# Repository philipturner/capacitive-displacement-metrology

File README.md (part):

# Capacitive Displacement Metrology

Phase 0.2/I/II of the [APM Roadmap](https://github.com/philipturner/apm-roadmap)

Objective: Finish a project that has dragged on for 14 months.

Deadline: April 31, 2026 for creepless imaging of graphite

Table of Contents:
- [December 15, 2025](#december-15-2025)
- [December 16, 2025](#december-16-2025)
- [December 18, 2025](#december-18-2025)
- [December 22, 2025](#december-22-2025)
- [January 3, 2026](#january-3-2026)
- [January 5, 2026](#january-5-2026)
- [January 6, 2026](#january-6-2026)
- [January 7, 2026](#january-7-2026)
- [January 8, 2026](#january-8-2026)
- [January 9, 2026](#january-9-2026)
- [January 12, 2026](#january-12-2026)
- [January 13, 2026](#january-13-2026)
- [January 14, 2026](#january-14-2026)
- [January 15, 2026](#january-15-2026)
- [January 16, 2026](#january-16-2026)
- [January 20, 2026](#january-20-2026)
- [January 24, 2026](#january-24-2026)
- [January 26, 2026](#january-26-2026)
- [January 29, 2026](#january-29-2026)
- [January 30, 2026](#january-30-2026)
- [February 2, 2026](#february-2-2026)
- [February 3, 2026](#february-3-2026)
- [February 11, 2026](#february-11-2026)
- [February 12, 2026](#february-12-2026)
- [February 17, 2026](#february-17-2026)
- [February 27, 2026](#february-27-2026)
- [March 8, 2026](#march-8-2026)
- [March 9, 2026](#march-9-2026)
- [March 10, 2026](#march-10-2026)
- [March 12, 2026](#march-12-2026)
- [March 20, 2026](#march-20-2026)
- [March 26, 2026](#march-26-2026)
- [March 28, 2026](#march-28-2026)
- [March 29, 2026](#march-29-2026)
- [April 2, 2026](#april-2-2026)
- [April 27, 2026](#april-27-2026)
- [May 4, 2026](#may-4-2026)
- [Jun 1, 2026](#jun-1-2026)
- [Jun 7, 2026](#jun-7-2026)
- [Jun 17, 2026](#jun-17-2026)

## December 15, 2025

$80,000 worth of wire transfers have hit the bank. I now have enough financial security to proceed with hardware work.

The first step is ensuring I can be paid a full-time salary. Comply with US tax laws, SEC regulations, etc. I predicted the exact numbers before going through the legal boilerplate and setup.

To save effort, serious work <i>probably</i> won't begin until Jan 2 2026. I can avoid filing a few tax return documents for the 2025 year. I will figure out some remaining tax and paperwork stuff during the last days of 2025.

Current estimate for the press release is Dec 18 2025.

## December 16, 2025

This is ridiculous. The United States is the only country where taxes are such a pain: https://www.propublica.org/article/inside-turbotax-20-year-fight-to-stop-americans-from-filing-their-taxes-for-free

## December 18, 2025

I want to make the creepless SPM happen in the shortest amount of time, and publish transparent data that can be fact-checked. To stay true to my motive, I made another attempt to persuade Robert Wolkow to cooperate. I could save many person-hours, recycling existing designs for creepless SPM hardware.

Regardless of whether he shares any design information, I will proceed according to plan. Any data published by other sources should be treated with extreme skepticism. Do not trust any other lab's data, except data gathered in my own house.

| Phase | Description | Voltage |
| ----: | ----------- | ------: |
| 0.2   | PZT metrology | 24&ndash;40 V |
| 1.1   | LiNbO3 metrology | 850 V |
| 1.2   | LiNbO3 kinematic mount | 850 V |
| 2.1   | LiNbO3 STM, graphite sample | 850 V |
| 2.2   | LiNbO3 STM, inverted mode tip registration | 850 V |

I can shortcut to an important milestone, without the expensive vacuum chamber. Just need to speed up the progress with tripod synthesis. No additional employees or contractors needed for hardware design.

At the end of Phase 0.2, we'll reflect on how long this phase took. If it happened quickly, we can reach the end goal with a single employee. Otherwise, I will probably hire a temporary contractor for hardware design. Phase 2.2 should be completed before Dec 31 2026.

> Nomenclature change: exclude Roman numerals from the phase names, at least when numbering sub-phases. It's highly cumbersome to process "I.1" and "II.2", versus "1.1" and "2.2".
>
> In addition, we may right-align the phase names in tables and spreadsheets.

## December 22, 2025

Still figuring out taxes, but making progress. Putting work on the next MNT animation on hold. Not really motivated when the response to the tutorial is anemic.

Figuring out the details of a possible contract with ChimiaDAO. Our funds should last us well beyond 6 months into the future: oversee completion of Phase 0.2, stable income while raising funds for the next round. Progress on the tripod synthesis will be reported in the Phase 0.2 repository, alongside hardware progress.

## January 3, 2026

We are now sufficiently ready to return to experiments. Paid labor will start on January 5. Rippling costs a ridiculous $1,800 sign-on contract over 18 months ($150 down payment). Definitely not what they publicly advertise or what you get from LLM summaries. In the future, we will face similar obfuscation of quotes from hardware suppliers (e.g. UHV-quality turbopumps cost $14,000 minimum).

## January 5, 2026

I will start by resolving an important unknown. How much does it cost to have 500 nm range instead of 80 nm range for the LiNbO3 piezos? This has implications all through Phase III, where we integrate a custom scanner into the vacuum chamber. It explodes the design cost in Phase III because Wolkow will likely be selling his own design. Already designed hardware is cheaper than the person-hours cost of designing new hardware.

https://www.matsusada.com/corporate/management.html

Might contact Matsusada after doing my own research on their products and my performance requirements.

https://www.matsusada.com/column/hvps-safty.html

### Modeling Power Supply Requirements

To be conservative, assume we'll need 3 kinematic mounts for X, Y, and Z. We're also reducing the range, with 6 plates from Wolkow's patent instead of 10. Now all actuators, for all axes, use 6-high piezo stacks. The capacitance of the kinematic mount probably prevents utilization of the PA94 for high slew rates.

Design options for piezo stack geometry:
- 6 plates, 5 mm x 5 mm area, 6 mm stack height
- 6 plates, 10 mm x 10 mm area, 6 mm stack height
- 10 plates, 10 mm x 10 mm area, 10 mm stack height

The plate area is important now, because smaller plates have less capacitance, and thus lower current pulse requirements for the power supply. We may also use different plate areas for the fine vs. coarse actuators. Mechanically, sticking two 5 mm x 5 mm stacks on top of each other would create a 12 mm high tower. Not a good idea.

### Modeling Piezo Force Requirements

To break static friction, the piezo needs to generate a certain amount of force. In addition to the range and waveform frequency requirements.

Assuming a 0.5 mm thick plate and 69.2 GPa shear modulus:

| Voltage | Displacement | Shear Proportion | Shear Pressure |
| ------: | -----------: | ---------------: | -------------: |
| 200 V   | 13.6 nm      | 2.72e-5          | 1.88e6 Pa      |
| 850 V   | 57.8 nm      | 1.16e-4          | 8.00e6 Pa      |

Forces for various setups at 200 V:

| Plate Size | Plate Count | Shear Force | Max Weight |
| ---------- | ----------: | ----------: | ---------: |
| 5 mm x 5 mm   | 1 | 47.1 N | 4.8 kg |
| 5 mm x 5 mm   | 3 | 141.1 N | 14.4 kg |
| 10 mm x 10 mm | 1 | 188.2 N | 19.2 kg |
| 10 mm x 10 mm | 3 | 564.7 N | 57.6 kg |

Forces for various setups at 850 V:

| Plate Size | Plate Count | Shear Force |
| ---------- | ----------: | ----------: |
| 5 mm x 5 mm   | 1 | 200.0 N | 20.4 kg |
| 5 mm x 5 mm   | 3 | 600.0 N | 61.2 kg |
| 10 mm x 10 mm | 1 | 800.0 N | 81.6 kg |
| 10 mm x 10 mm | 3 | 2399.9 N | 244.9 kg |

Even though shear force doesn't increase with the number of plates per stack, the above numbers should exceed all reasonable force requirements.

### Modeling Required Slew Rate

Dive deeper into the waveform requirements for stick-slip nanopositioning:
- Does the waveform need to contain components above the resonance frequency?
- What is the target rate in steps/second?
- Why is woodpecker coarse tip approach so slow?

These variables can probably be resolved at a later date. I mostly want a lower capacitance in the kinematic mount, while still attaining 30 V/μs slew rate of the PA95 op amp.

### Design Space Exploration

Quiescent current demands on power supply:
- Conservatively 6 DAC channels and 6 PA95 op amps for Phase III
- 6 * 2.2 mA = 13.2 mA

Capacitance (in pF) of entire kinematic mount:
- Piezo plate count is 18 (3 stacks, each with 6 plates)
- Dielectric constant of lithium niobate at 300 K is 88
- Thickness of each plate is 0.5 mm

| Configuration | Capacitance |
| ------------- | ----------: |
| 5 mm x 5 mm   | 701         |
| 10 mm x 10 mm | 2805        |

Current (in mA) required to drive the kinematic mount:

| Configuration | 30 V/μs | 20 V/μs | 10 V/μs | 5 V/μs | 3 V/μs |
| ------------- | ------: | ------: | ------: | -----: | -----: |
| 5 mm x 5 mm   | 21.0    | 14.0    | 7.0     | 3.5    | 2.1    |
| 10 mm x 10 mm | 84.2    | 56.1    | 28.1    | 14.0   | 8.4    |

Power (in W) generated by either of the 450 V power supplies:
- Each supply operates at ~50% duty cycle
- Each supply operates during the respective edge of the waveform
  - +450 V for rising
  - -450 V for falling

| Configuration | 30 V/μs | 20 V/μs | 10 V/μs | 5 V/μs | 3 V/μs |
| ------------- | ------: | ------: | ------: | -----: | -----: |
| 5 mm x 5 mm   | 9.5     | 6.3     | 3.2     | 1.6    | 0.9    |
| 10 mm x 10 mm | 37.9    | 25.2    | 12.6    | 6.3    | 3.8    |

Frequency of an 850 V triangle wave:

| Slew rate (V/μs)     | 30   | 20   | 10  | 5   | 3   |
| -------------------- | ---: | ---: | --: | --: | --: |
| Rise time (μs)       | 28   | 43   | 85  | 170 | 283 |
| Wave period (μs)     | 57   | 85   | 170 | 340 | 567 |
| Wave frequency (kHz) | 17.6 | 11.8 | 5.9 | 2.9 | 1.8 |

### Final Current Demands

Making the smart design choice to use 5 mm instead of 10 mm piezo plates for the kinematic mount.

Providing two negotiable options for maximum waveform frequency: 5.9 kHz, 17.6 kHz

| Wave frequency                        | 5.9 kHz  | 17.6 kHz |
| ------------------------------------- | -------: | -------: |
| Quiescent current                     | 13.2 mA  | 13.2 mA  |
| Current of one active kinematic mount |  7.0 mA  | 21.0 mA  |
| Peak current in either 450 V supply   | 20.2 mA  | 34.2 mA  |
| Peak power in either 450 V supply     | 9.1 W    | 15.4 W   |
| Average power in either 450 V supply  | 7.5 W    | 10.7 W   |
| Total power in both supplies combined | 15.0 W   | 21.3 W   |

I will state the peak (not average) demands when emailing Matsusada.

## January 6, 2026

Still waiting to hear back. Customer service things tend to take a long time, and have many delays.

Where else can I make progress regarding the pathway to a final-state LiNbO3 SPM? The design of a custom UHV chamber with custom electrical feedthroughs. Not the UHV-SPM system that Wolkow might be selling.

### Sample Preparation Concerns

Monocrystalline Au(111) surfaces are indeed very expensive. Most vendors obfuscate the prices. I recall one vendor on Google Search showing $2,400. Several months ago, I remember a different vendor saying $3,000 publicly. There's a research paper about reducing the cost of Au(111) surface production: https://pubs.acs.org/doi/full/10.1021/acsnano.4c17431

I will start with trying to reproduce Dan Berard's results, with my imperfect Au(111) "textured" surface prepared at Virginia Tech. Next, reproduce the self-assembled monolayer structure of densely packed tripods on gold. If everything works well, attempt a sparse monolayer that can generate reverse-phase images (RPIs) from the CBN paper.

I'm highly skeptical this will work out. We may need complicated EC-STM or $3,000 pristine commercial gold samples. However, both of these are cheaper/better than a complete UHV chamber.

The end state of this sample preparation must be something actually usable for inverted mode mechanosynthesis.

---

<b>Second concern:</b> do we need to bake off the Au surface prior to entering into the UHV chamber? That would remove all the tripods deposited in solution. I want to avoid the vapor-phase deposition of tripods onto gold, that previous literature used.

<b>Worst case:</b> final vacuum system requires complicated and expensive MBE and/or XPS hardware. But the chemical design space for Au-S linkers is still unlocked.

---

Other important preliminary tasks to remember:
- What is going on with the crystallographic vectors and shear directions for 41 X-cut lithium niobate?
  - Does some extra displacement happen in the off-axis direction?
  - What is the physical (atomic) justification for perfect 90 degree misalignment between E-field and position displacement?
  - Lithium niobate is symmetric, so there should be multiple directions where such a coupling occurs.
  - Might use [Molecular Renderer](https://github.com/philipturner/molecular-renderer) to visualize crystal atoms and control programmable animations.
- Why is coarse tip approach so slow?

### Update

Got the first email response back from Matsusada. Working on the next steps regarding our discussion.

Regarding electrical feedthroughs for vacuum systems: it boils down to dielectric breakdown and [Paschen's curve](https://en.wikipedia.org/wiki/Paschen%27s_law#/media/File:Paschen_curves.svg). I don't think I need to spend much additional time on this topic, for now.

I'll call it a day for now. Tomorrow, I will investigate the crystallographic vectors of lithium niobate.

## January 7, 2026

The Islam and Beamish (2018) precursor paper corrects for the effect of the 41° angle on the piezo constant. They measured a 23 ppm change in capacitance at 300 μm. Voltage was 40 V and there were 3 plates in the stack. Raw data for piezo constant should be 57.5 pm/V, but they stated 49.7 pm/V in the paper. I reproduced the ratio of 57.5 vs 49.7 when simulating the response of 41° vs 0° cut lithium niobate.

I think positive 41° means the manufacturer rotated the crystal boule by that amount. The reference plane ready to slice a wafer hasn't moved. This explains why the script has to invert the rotation angle to match literature data.

Wafers from Crystal Substrates have no special 41° rotation. They are xyt 0° in IRE notation. Provided that you select "X-cut (1 1 2-bar 0)".

---

[PiezoelectricCoefficients2.swift](./Code/Simulation/PiezoelectricCoefficients2.swift)

The actual shear constant is 80 pm/V, in a direction 32° counterclockwise from Z (0 0 0 1). The electric field is always being applied across the X-axis, regardless of the rotation of the wafer cut. If Wolkow has realized this, then the 80 nm quoted from the patent corresponds to 167 V at 6 piezo plates. Not 196 V.

```
swift PiezoelectricCoefficients2.swift 0

// 0°
//  ∂(∂u/∂x1)/∂E1: SIMD3<Float>(0.0, -21.0, 34.0) pm/V
//  ∂(∂u/∂x2)/∂E1: SIMD3<Float>(-21.0, 0.0, 0.0) pm/V
//  ∂(∂u/∂x3)/∂E1: SIMD3<Float>(34.0, 0.0, 0.0) pm/V

// 0°
//  u (x-axis): [0.0, -17.9, 28.9] nm
//  u (y-axis): [-178.5, 0.0, 0.0] nm
//  u (z-axis): [289.0, 0.0, 0.0] nm

// 0°
//  u (x-axis): [0.0, -35.7, 57.8] nm
//  u (y-axis): [0.0, 0.0, 0.0] nm
//  u (z-axis): [0.0, 0.0, 0.0] nm
```

```
swift PiezoelectricCoefficients2.swift 32

// 32°
//  ∂(∂u/∂x1)/∂E1: SIMD3<Float>(0.0, 0.20824544, 39.961945) pm/V
//  ∂(∂u/∂x2)/∂E1: SIMD3<Float>(0.20824254, 0.0, 0.0) pm/V
//  ∂(∂u/∂x3)/∂E1: SIMD3<Float>(39.961945, 0.0, 0.0) pm/V

// 32°
//  u (x-axis): [0.0, 0.2, 34.0] nm
//  u (y-axis): [1.8, 0.0, 0.0] nm
//  u (z-axis): [339.7, 0.0, 0.0] nm

// 32°
//  u (x-axis): [0.0, 0.4, 67.9] nm
//  u (y-axis): [0.0, 0.0, 0.0] nm
//  u (z-axis): [0.0, 0.0, 0.0] nm
```

```
swift PiezoelectricCoefficients2.swift 41

// 41°
//  ∂(∂u/∂x1)/∂E1: SIMD3<Float>(0.0, 6.4571033, 39.437363) pm/V
//  ∂(∂u/∂x2)/∂E1: SIMD3<Float>(6.4571033, 0.0, 0.0) pm/V
//  ∂(∂u/∂x3)/∂E1: SIMD3<Float>(39.437366, 0.0, 0.0) pm/V

// 41°
//  u (x-axis): [0.0, 5.5, 33.5] nm
//  u (y-axis): [54.9, 0.0, 0.0] nm
//  u (z-axis): [335.2, 0.0, 0.0] nm

// 41°
//  u (x-axis): [0.0, 11.0, 67.0] nm
//  u (y-axis): [0.0, 0.0, 0.0] nm
//  u (z-axis): [0.0, 0.0, 0.0] nm
```

If we double the plate Y and Z dimensions to 10 mm, the 41 degree case changes from 54.9 to 109.8 nm, and from 335.2 to 670.4 nm. But after correcting for the ratio of X dimension to Y or Z dimension and summing into the X-axis shear, the true displacement is still 11.0 nm and 67.0 nm.

---

The X axis of the crystal boule doesn't create any charge when compressed. It cannot, because the crystal structure is symmetric across the YZ plane. The Y and Z axes in IRE notation are piezoelectric. That explains why they produce displacements.

I can imagine 6 symmetry operations for a valid pair of E-field axis and shear direction. The shear piezo constant is 80 pm/V, not 68 pm/V.

| X, Y, Z Principal Axes | Shear Direction |
| ---------------------- | -----------: |
| standard IRE orientation                       | Z rotated +32° counterclockwise about X |
| rotate X, Y by  +60° counterclockwise around Z | Z rotated -32° counterclockwise about X |
| rotate X, Y by +120° counterclockwise around Z | Z rotated +32° counterclockwise about X |
| rotate X, Y by +180° counterclockwise around Z | Z rotated -32° counterclockwise about X |
| rotate X, Y by +240° counterclockwise around Z | Z rotated +32° counterclockwise about X |
| rotate X, Y by +300° counterclockwise around Z | Z rotated -32° counterclockwise about X |

Due to the IRE standard, readily stocked commercial wafers only fall in the first row. But in theory, there are 5 other crystal cuts with the same piezoelectric response. Rows 3 and 5 are equivalent to row 1 by a symmetry operation. Thus, the IRE standard has prevented the opposite chirality of X-cut lithium niobate (rows 2, 4, 6) from ever reaching the market.

In Islam and Beamish (2018), the erroneous off-axis displacement would not be measured. Moving the parallel plates in a direction parallel to each other, will decrease the capacitance no matter which direction it moves. The case of zero off-axis displacement is a local maximum of capacitance. The first derivative with respect to position is zero. In contrast, the first derivative with respect to on-axis displacement (distance between the two plates) is very high. It is the only component that could affect the measurements.

## January 8, 2026

I did some investigation of why coarse tip approach is slow. There are three limiting factors:
- Allowed positional excursion before tip crashes, relative to point of minimum detectable current
- Delay for sensor to register the tip's new position
- Inertial overshoot even after the piezo stops applying force

At the speeds we're moving, capacitive currents have no effect on measurements.

| Bias Voltage | dC/dx | dx/dt | Capacitive Current |
| -----------: | ----: | ----: | -----------------: |
| 1 V          | 1.50e-10 F/m | 5.88 μm/s | 0.9 fA |
| 3 V          | 1.50e-10 F/m | 5.88 μm/s | 2.6 fA |

The allowed positional excursion was set to 280 pm, the difference between 1 nA and 313 fA at 80 pm/decade. True tip crash likely occurs at 10 nA, or a limit of 360 pm. To improve the safety margin, the target displacement is half of the 280 pm range, or 140 pm.

Next, the delay of the sensor. Although Dan Berard and similar STMs may have an ADC bandwidth of 200 kHz, the limiter is the ~10 kHz pole of the 100 MΩ TIA design. I also conservatively derated the ADS8699 from 15 kHz to 10 kHz. The limiter here is not digitization frequency, but rather the analog response latency from the lowpass filter.

If we model the delay as limitations on sinewave frequency, we get 10 kHz. That was used for calculations in the screenshot above. If we model it as exponential decay with a time constant of RC, we only need 2 or 3 time constants (settling to 13.5% or 5.0%), not 2π time constants. I'll correct for this in a bit.

Finally, the vibrational excursion. This is easier to model than I anticipated. The velocity is the angular frequency at resonance, times the positional amplitude of the vibration. I used [3340 Hz](https://github.com/philipturner/transimpedance-amplifier?tab=readme-ov-file#september-9-2025) eigenfrequency from FEM simulations, which is better than most STMs.

In the screenshot above, the maximum acceptable velocity was 0.95 μm/s.

### Correction for more optimistic sensor response time

| RC Time Constants | Sensor Error from Lag | Proportion of Limit from Vibrational Excursion | Maximum Acceptable Velocity |
| ----------------: | --------------------: | ---------------------------------------------: | --------------------------: |
| 6.28              | 0.2%                  | 32.1% | 0.95 μm/s |
| 3.00              | 5.0%                  | 49.8% | 1.47 μm/s |
| 2.00              | 13.5%                 | 59.8% | 1.77 μm/s |
| 1.00              | 36.7%                 | 74.9% | 2.21 μm/s |

Anything shorter than 3 RC time constants seems questionable. I'll set the revised velocity to 1.47 μm/s.

---

Next, walk through the algorithm for coarse displacements during tip approach.

Start with a conservatively slow waveform. The time to move the tip during the coarse steps is a tiny fraction of the overall time during coarse approach. Start with a 1 kHz triangle wave, 850 V peak-to-peak amplitude, or ±425 V. Displacement range is 408 nm, or ±204 nm. Each edge of the wave form takes 500 μs. Slew rate is 1.7 V/μs, much less than the PA95's limit of 30 V/μs. Speed is 816 μm/s. The kinematic mount moves back and forth at 816 μm/s in alternating directions, always returning to the same position.

| Kinematic Mount | Mass of Load | Equivalent Gravitational Force | Force in Pounds |
| --------------- | -----------: | -----------------------------: | --------------: |
| X Axis          | 13.02 g      | 127.6 mN | 0.03 lb |
| Y Axis          | 23.37 g      | 229.0 mN | 0.05 lb |
| Z Axis          | 8.94 g       | 87.6 mN  | 0.02 lb |

---

Using the N42 grade of magnets.

Magnets need to be extremely close to the surface, to achieve optimal force. I'm setting 300 μm tolerance as the practical upper limit, which nerfs magnetic force ~50% for my geometry. The smaller X and Z kinematic mount can use two 5 mm magnets, while the Y kinematic mount can use four.

Playing around with parameters on: https://www.kjmagnetics.com/magnet-strength-calculator.asp?srsltid=AfmBOorsJBupnrQ9hcxNIcvuajbopfTptJDigBCl6Y_YctyCHKSyzlxy

| Diameter | Thickness | Distance | Pull Force Case 1 |
| -------: | --------: | -------: | ----------------: |
| 5 mm     | 3 mm      | 0.0 mm   | 1.45 lb           |
| 5 mm     | 5 mm      | 0.0 mm   | 2.04 lb           |
| 5 mm     | 7 mm      | 0.0 mm   | 2.19 lb           |
| 10 mm    | 3 mm      | 0.0 mm   | 4.33 lb           |
| 10 mm    | 5 mm      | 0.0 mm   | 6.48 lb           |
| 10 mm    | 7 mm      | 0.0 mm   | 7.73 lb           |

| Diameter | Thickness | Distance | Pull Force Case 1 |
| -------: | --------: | -------: | ----------------: |
| 5 mm     | 3 mm      | 0.3 mm   | 0.73 lb           |
| 5 mm     | 5 mm      | 0.3 mm   | 1.05 lb           |
| 5 mm     | 7 mm      | 0.3 mm   | 1.15 lb           |
| 10 mm    | 3 mm      | 0.3 mm   | 2.75 lb           |
| 10 mm    | 5 mm      | 0.3 mm   | 4.19 lb           |
| 10 mm    | 7 mm      | 0.3 mm   | 5.07 lb           |

| Diameter | Thickness | Distance | Pull Force Case 1 |
| -------: | --------: | -------: | ----------------: |
| 5 mm     | 3 mm      | 1.0 mm   | 0.29 lb           |
| 5 mm     | 5 mm      | 1.0 mm   | 0.44 lb           |
| 5 mm     | 7 mm      | 1.0 mm   | 0.50 lb           |
| 10 mm    | 3 mm      | 1.0 mm   | 1.50 lb           |
| 10 mm    | 5 mm      | 1.0 mm   | 2.36 lb           |
| 10 mm    | 7 mm      | 1.0 mm   | 2.90 lb           |

We do need two magnets aligned in the center of the path of motion. Both Voigtlander and Wolkow's reference designs do this. We can just tweak the force for the Y-axis magnets to be doubled.

All numbers in the above tables are an order of magnitude greater than the amount required to counteract gravity. I will use a design where all kinematic mounts are 45° away from perfectly vertical, and the Y axis's direction of motion is perpendicular to gravity. That does not remove the disparity in load mass between kinematic mounts; it just seems like the most sensible geometry.

To start, let's set the magnet force to 0.50 lb (2.22 N) for all kinematic mounts. This is probably too large, but we can correct it later if needed. In addition, the coefficient of static friction is 0.5 and the coefficient of kinetic friction is either 0.3 or 0.4. We want to explore a combinatorial space for uncertainty in the nature of friction. Finally, the transition from stationary to the "riding" part of the waveform is smoothed out enough to not break static friction. The computer code controlling the DAC makes this part of the waveform smooth.

---

Another interesting observation is the disparity between resonance frequencies relevant to this analysis, and resonant frequency of the tip-sample mechanical loop (3340 Hz). We are localizing the analysis to the kinematic mount subsystem, which is much stiffer and spatially smaller than the whole STM. In addition, we are not examining any possible mode (the floppiest mode), but the direction of vibration parallel to motion. What we need to worry about regarding minimum eigenfrequencies, is coupling to other floppier modes and exciting them. We prevent this by only repeating the sawtooth waveform at a 1 kHz frequency. Thus, extremely high frequencies of ~50 kHz could define settling times for stick-slip action.

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
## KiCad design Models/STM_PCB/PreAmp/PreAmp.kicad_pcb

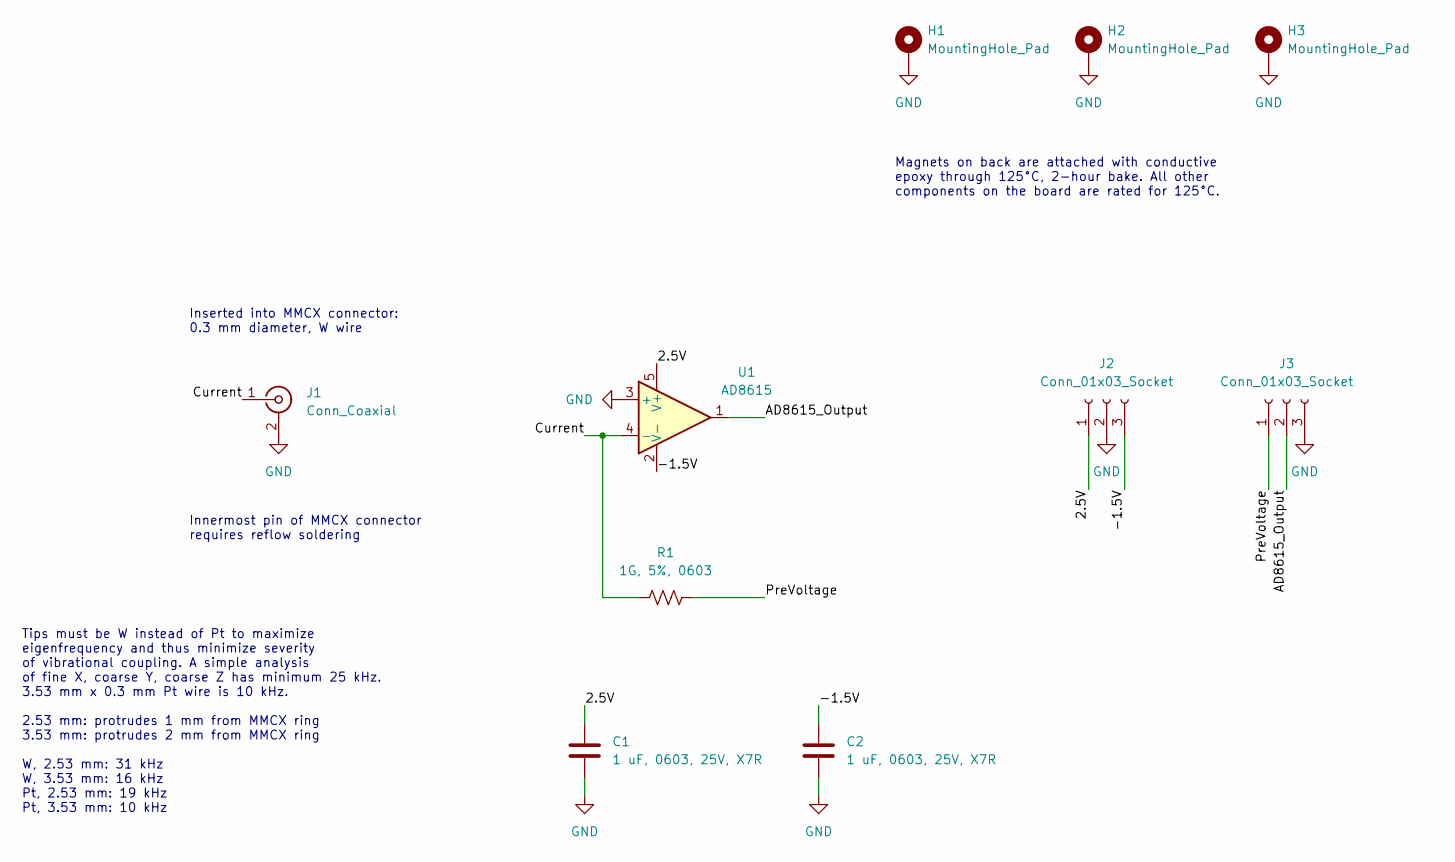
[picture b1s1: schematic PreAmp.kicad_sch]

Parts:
C1, C2: 1 uF, 0603, 25V, X7R; CAPC0603
H1, H2, H3: MountingHole_Pad; KJ_D21SH
J1: Conn_Coaxial; Samtec_MMCX_SMT
J2, J3: Conn_01x03_Socket; PinSocket_1x3_SMT
R1: 1G, 5%, 0603; RESC0603
U1: AD8615

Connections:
/2.5V: C1.1, J2.1, U1.5 (V+)
/-1.5V: C2.1, J2.3, U1.2 (V-)
/AD8615_Output: J3.2, U1.1
/Current: J1.1 (In), R1.1, U1.4 (-)
/PreVoltage: J3.1, R1.2
GND: C1.2, C2.2, H1.1, H2.1, H3.1, J1.2 (Ext), J2.2, J3.3, U1.3 (+)

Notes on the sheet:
Tips must be W instead of Pt to maximize eigenfrequency and thus minimize severity of vibrational coupling. A simple analysis of fine X, coarse Y, coarse Z has minimum 25 kHz. 3.53 mm x 0.3 mm Pt wire is 10 kHz. 2.53 mm: protrudes 1 mm from MMCX ring 3.53 mm: protrudes 2 mm from MMCX ring W, 2.53 m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
Inserted into MMCX connector: 0.3 mm diameter, W wire
Magnets on back are attached with conductive epoxy through 125°C, 2-hour bake. All other components on the board are rated for 125°C.
Innermost pin of MMCX connector requires reflow soldering

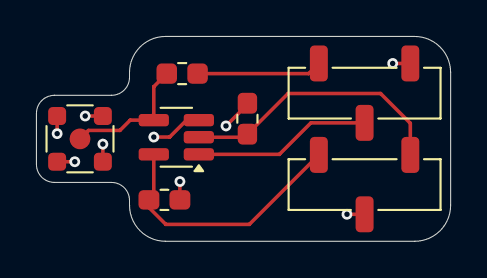
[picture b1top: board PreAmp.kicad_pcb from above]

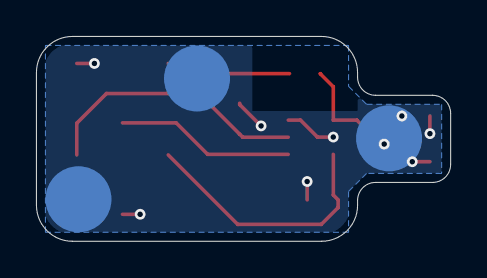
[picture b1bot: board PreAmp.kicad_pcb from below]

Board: 2 copper layers, 23.0 x 11.4 mm, 10 parts (3 on the bottom side), 6 nets.

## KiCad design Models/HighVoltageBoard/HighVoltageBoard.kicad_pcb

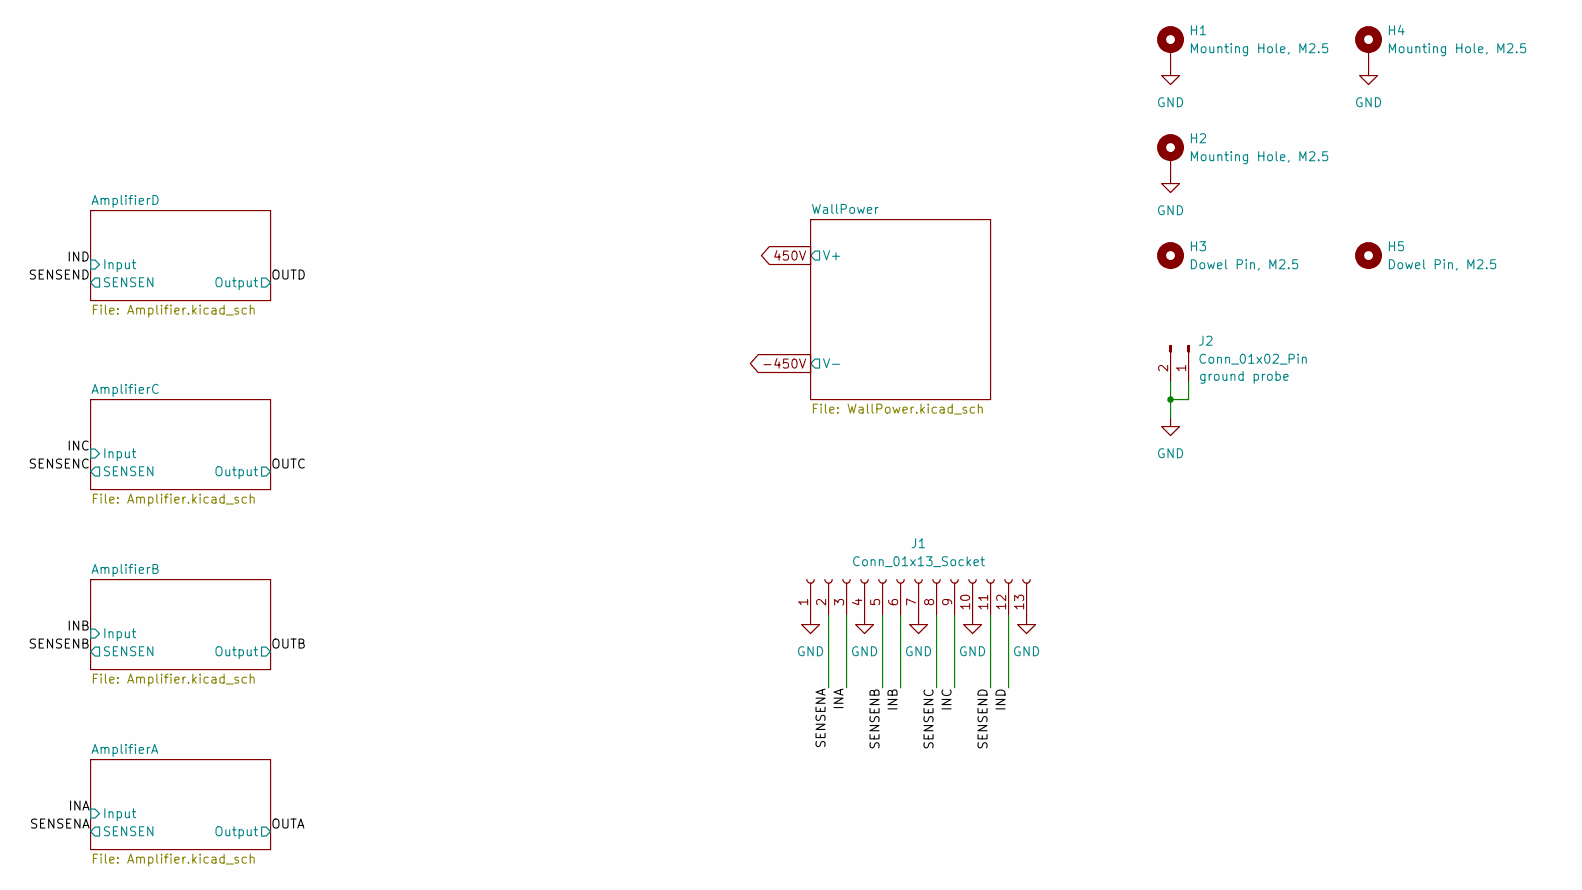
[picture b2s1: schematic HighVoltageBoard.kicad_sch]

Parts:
H1, H2, H4: Mounting Hole, M2.5; Keystone_24929
H3, H5: Dowel Pin, M2.5; DowelPin_2.5mm
J1: Conn_01x13_Socket; PinSocket_1x13
J2: Conn_01x02_Pin; PinHeader_1x2

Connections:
/INA: J1.3; also elsewhere on the board
/INB: J1.6; also elsewhere on the board
/INC: J1.9; also elsewhere on the board
/IND: J1.12; also elsewhere on the board
/SENSENA: J1.2; also elsewhere on the board
/SENSENB: J1.5; also elsewhere on the board
/SENSENC: J1.8; also elsewhere on the board
/SENSEND: J1.11; also elsewhere on the board
GND: H1.1, H2.1, H4.1, J1.1, J1.4, J1.7, J1.10, J1.13, J2.1, J2.2; also elsewhere on the board

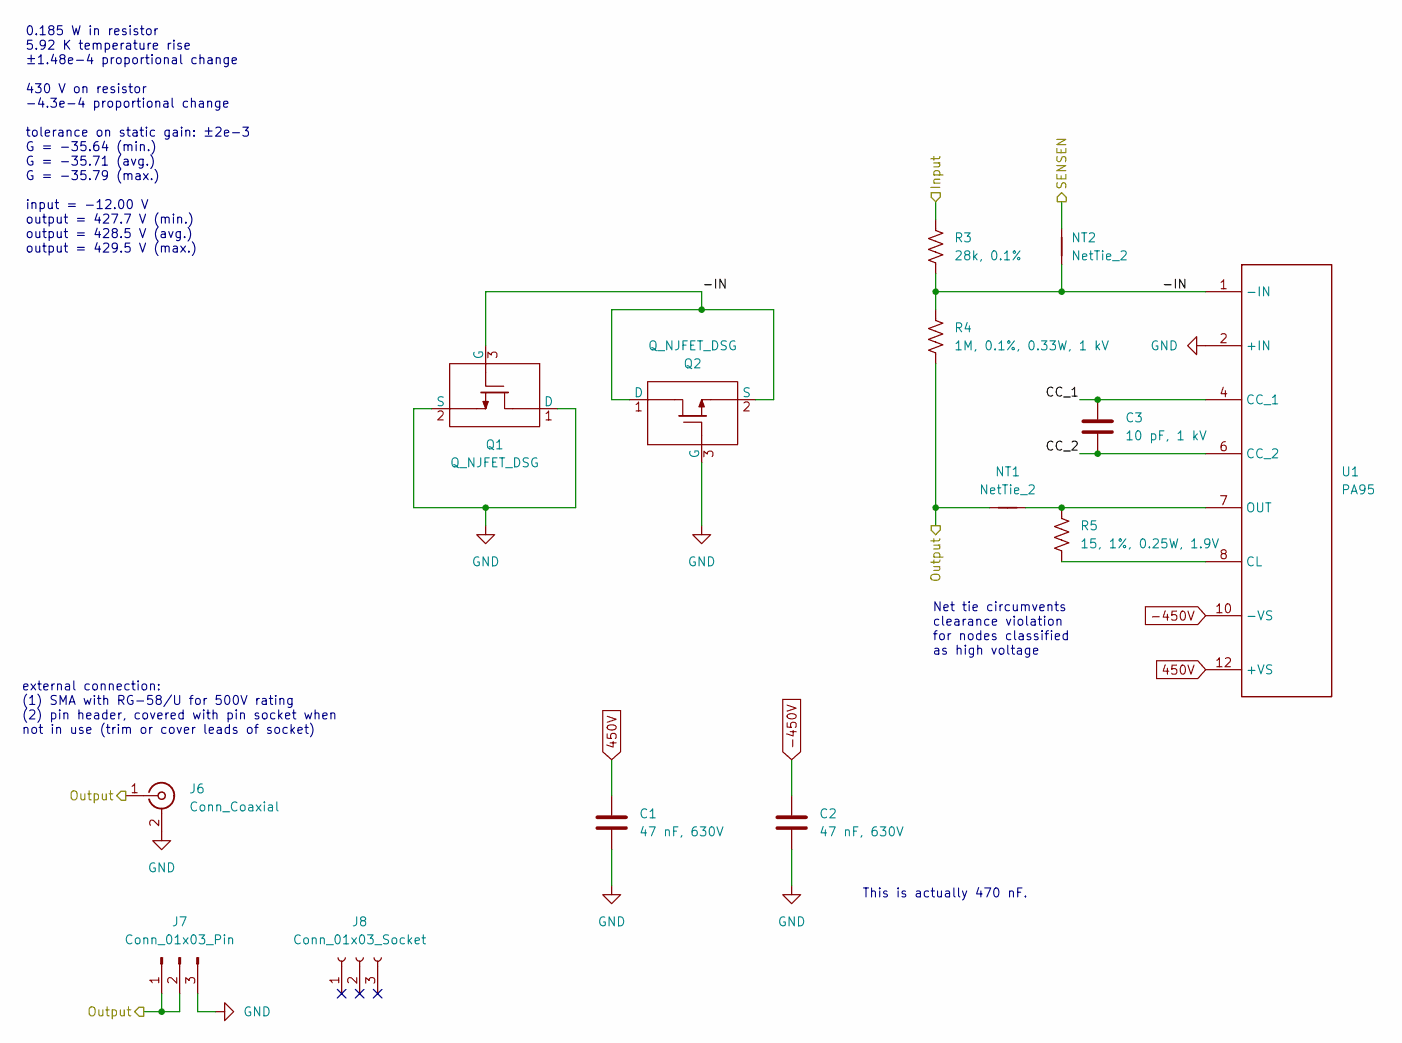
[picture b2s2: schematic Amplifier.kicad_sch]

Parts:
C1, C2: 47 nF, 630V; CAPC2220_GRJ
C3: 10 pF, 1 kV; CAPC1206_CHV
J6: Conn_Coaxial; RFPC-SMA27-F
J7: Conn_01x03_Pin; PinHeader_1x3
J8: Conn_01x03_Socket
NT1: NetTie_2; NetTie_0.2mm_HighVoltage
NT2: NetTie_2; NetTie_0.2mm
Q1, Q2: Q_NJFET_DSG; SOT-23
R3: 28k, 0.1%; RESC0603
R4: 1M, 0.1%, 0.33W, 1 kV; RESC1210_TNPV
R5: 15, 1%, 0.25W, 1.9V; RESC0805
U1: PA95

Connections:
450V: C1.1, U1.12 (+VS); also elsewhere on the board
-450V: C2.1, U1.10 (-VS); also elsewhere on the board
/AmplifierA/-IN: NT2.1, Q1.3 (G), Q2.1 (D), Q2.2 (S), R3.2, R4.1, U1.1 (-IN)
/AmplifierA/CC_1: C3.1, U1.4 (CC_1)
/AmplifierA/CC_2: C3.2, U1.6 (CC_2)
/INA: R3.1; also elsewhere on the board
/OUTA: J6.1 (In), J7.1, J7.2, NT1.1, R4.2
/SENSENA: NT2.2; also elsewhere on the board
GND: C1.2, C2.2, J6.2 (Ext), J7.3, Q1.1 (D), Q1.2 (S), Q2.3 (G), U1.2 (+IN); also elsewhere on the board
unnamed: R5.1, U1.8 (CL)
unnamed: NT1.2, R5.2, U1.7 (OUT)

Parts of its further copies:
C4, C5, C7, C8, C10, C11: 47 nF, 630V; CAPC2220_GRJ
C6, C9, C12: 10 pF, 1 kV; CAPC1206_CHV
J9, J12, J15: Conn_Coaxial; RFPC-SMA27-F
J10, J13, J16: Conn_01x03_Pin; PinHeader_1x3
NT3, NT5, NT7: NetTie_2; NetTie_0.2mm_HighVoltage
NT4, NT6, NT8: NetTie_2; NetTie_0.2mm
Q3, Q4, Q5, Q6, Q7, Q8: Q_NJFET_DSG; SOT-23
R6, R9, R12: 28k, 0.1%; RESC0603
R7, R10, R13: 1M, 0.1%, 0.33W, 1 kV; RESC1210_TNPV
R8, R11, R14: 15, 1%, 0.25W, 1.9V; RESC0805
U2, U3, U4: PA95

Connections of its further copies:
450V: C4.1, C7.1, C10.1, U2.12 (+VS), U3.12 (+VS), U4.12 (+VS); also elsewhere on the board
-450V: C5.1, C8.1, C11.1, U2.10 (-VS), U3.10 (-VS), U4.10 (-VS); also elsewhere on the board
/AmplifierB/-IN: NT4.1, Q3.3 (G), Q4.1 (D), Q4.2 (S), R6.2, R7.1, U2.1 (-IN)
/AmplifierB/CC_1: C6.1, U2.4 (CC_1)
/AmplifierB/CC_2: C6.2, U2.6 (CC_2)
/AmplifierC/-IN: NT6.1, Q5.3 (G), Q6.1 (D), Q6.2 (S), R9.2, R10.1, U3.1 (-IN)
/AmplifierC/CC_1: C9.1, U3.4 (CC_1)
/AmplifierC/CC_2: C9.2, U3.6 (CC_2)
/AmplifierD/-IN: NT8.1, Q7.3 (G), Q8.1 (D), Q8.2 (S), R12.2, R13.1, U4.1 (-IN)
/AmplifierD/CC_1: C12.1, U4.4 (CC_1)
/AmplifierD/CC_2: C12.2, U4.6 (CC_2)
/INB: R6.1; also elsewhere on the board
/INC: R9.1; also elsewhere on the board
/IND: R12.1; also elsewhere on the board
/OUTB: J9.1 (In), J10.1, J10.2, NT3.1, R7.2
/OUTC: J12.1 (In), J13.1, J13.2, NT5.1, R10.2
/OUTD: J15.1 (In), J16.1, J16.2, NT7.1, R13.2
/SENSENB: NT4.2; also elsewhere on the board
/SENSENC: NT6.2; also elsewhere on the board
/SENSEND: NT8.2; also elsewhere on the board
GND: C4.2, C5.2, C7.2, C8.2, C10.2, C11.2, J9.2 (Ext), J10.3, J12.2 (Ext), J13.3, J15.2 (Ext), J16.3, Q3.1 (D), Q3.2 (S), Q4.3 (G), Q5.1 (D), Q5.2 (S), Q6.3 (G), Q7.1 (D), Q7.2 (S), Q8.3 (G), U2.2 (+IN), U3.2 (+IN), U4.2 (+IN); also elsewhere on the board
unnamed: R8.1, U2.8 (CL)
unnamed: NT3.2, R8.2, U2.7 (OUT)
unnamed: R11.1, U3.8 (CL)
unnamed: NT5.2, R11.2, U3.7 (OUT)
unnamed: R14.1, U4.8 (CL)
unnamed: NT7.2, R14.2, U4.7 (OUT)

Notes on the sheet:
This is actually 470 nF.
external connection: (1) SMA with RG-58/U for 500V rating (2) pin header, covered with pin socket when not in use (trim or cover leads of socket)
0.185 W in resistor 5.92 K temperature rise ±1.48e-4 proportional change 430 V on resistor -4.3e-4 proportional change tolerance on static gain: ±2e-3 G = -35.64 (min.) G = -35.71 (avg.) G = -35.79 (max.) input = -12.00 V output = 427.7 V (min.) output = 428.5 V (avg.) output = 429.5 V (max.)
Net tie circumvents clearance violation for nodes classified as high voltage

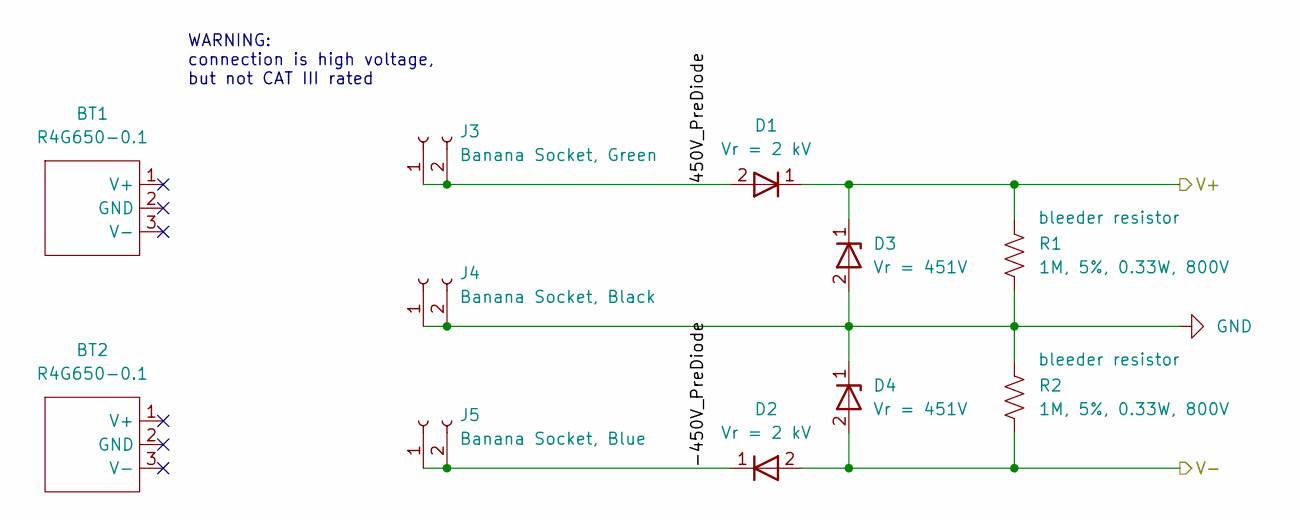
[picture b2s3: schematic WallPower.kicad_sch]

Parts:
BT1, BT2: R4G650-0.1
D1, D2: Vr = 2 kV; DO-214AC
D3, D4: Vr = 451V; DO-214AA
J3: Banana Socket, Green; Multicomp_24.243
J4: Banana Socket, Black; Multicomp_24.243
J5: Banana Socket, Blue; Multicomp_24.243
R1, R2: 1M, 5%, 0.33W, 800V; RESC1206_RCV

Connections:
450V: D1.1 (K), D3.1 (K), R1.1; also elsewhere on the board
-450V: D2.2 (A), D4.2 (A), R2.2; also elsewhere on the board
/WallPower/450V_PreDiode: D1.2 (A), J3.1, J3.2
/WallPower/-450V_PreDiode: D2.1 (K), J5.1, J5.2
GND: D3.2 (A), D4.1 (K), J4.1, J4.2, R1.2, R2.1; also elsewhere on the board

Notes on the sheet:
WARNING: connection is high voltage, but not CAT III rated

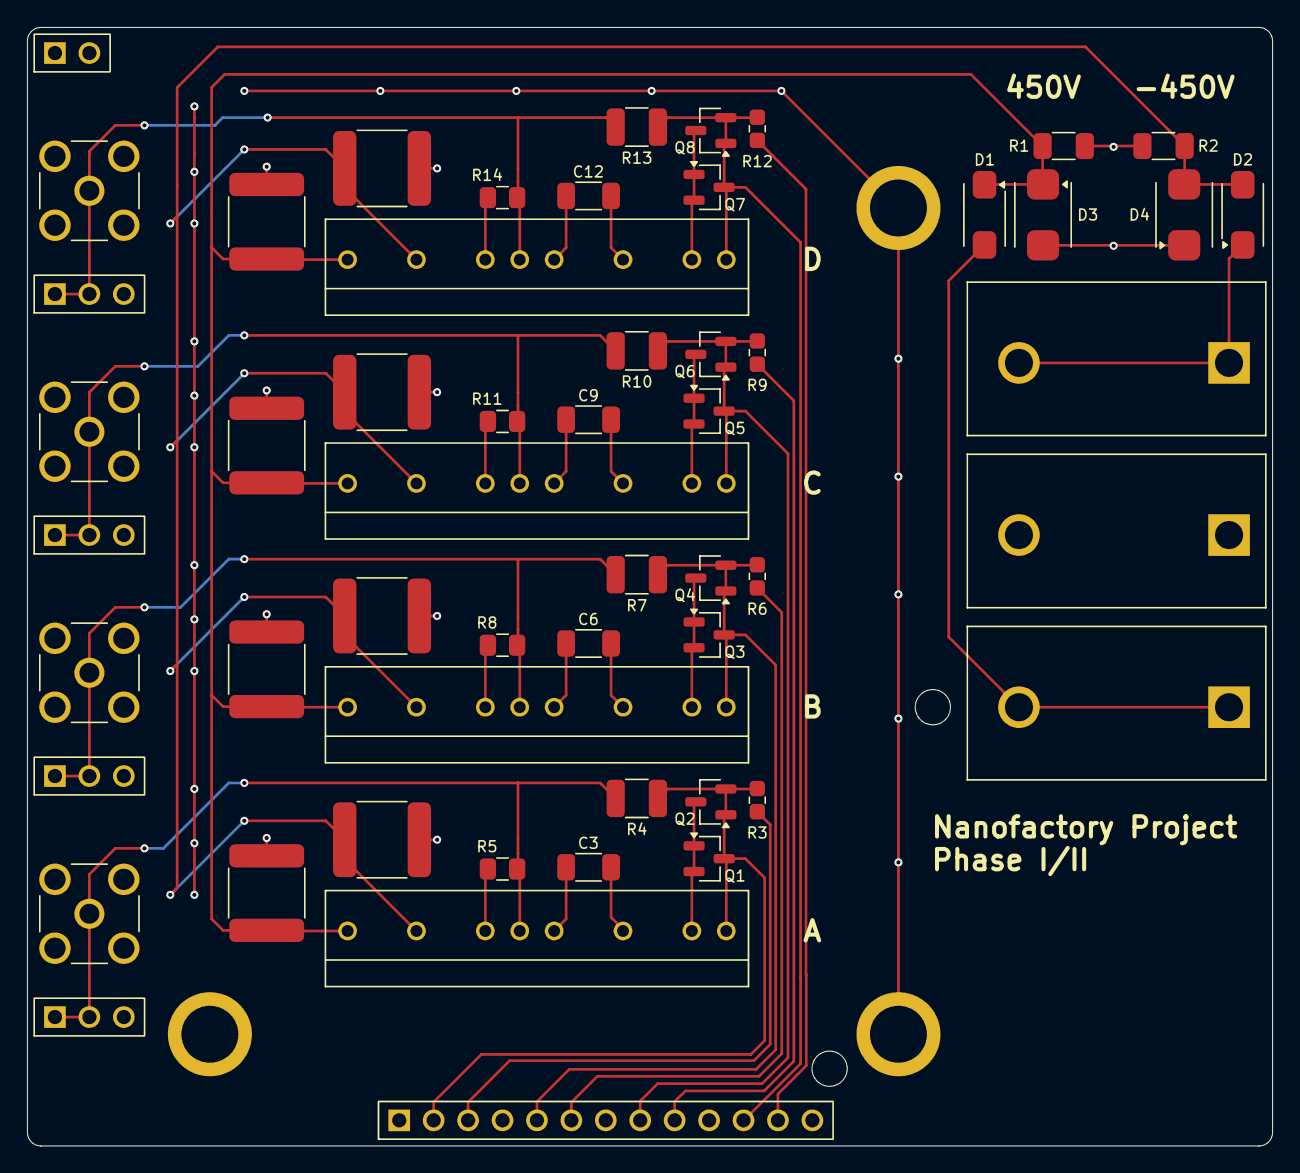
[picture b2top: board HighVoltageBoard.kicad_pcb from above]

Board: 2 copper layers, 91.9 x 82.5 mm, 68 parts (0 on the bottom side), 37 nets.

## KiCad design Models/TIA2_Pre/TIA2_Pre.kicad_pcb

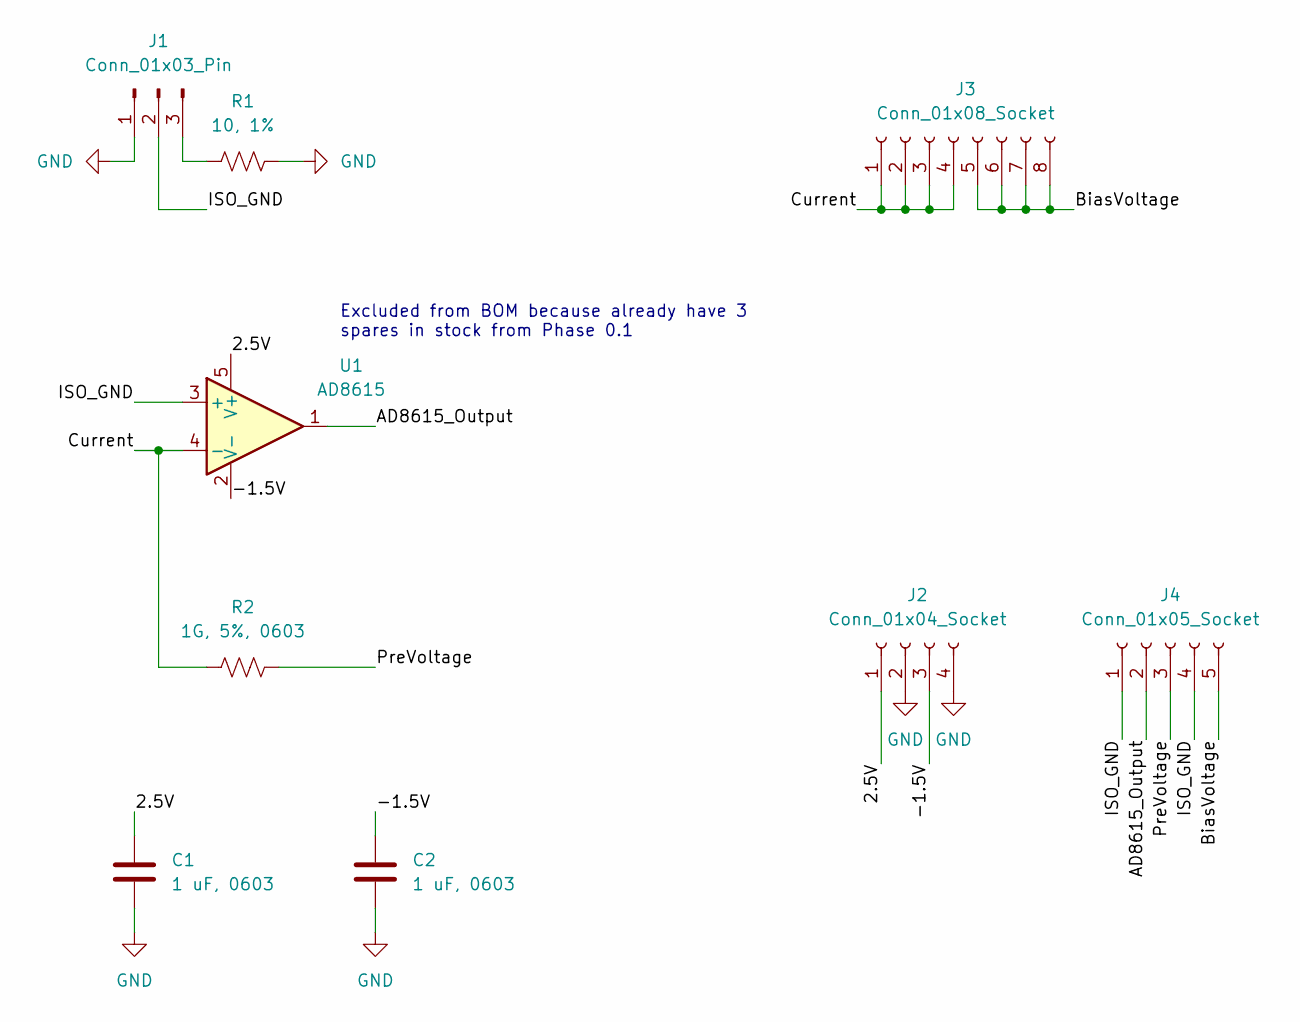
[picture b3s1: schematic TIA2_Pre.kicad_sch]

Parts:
C1, C2: 1 uF, 0603; CAPC0603
J1: Conn_01x03_Pin; PinHeader_1x3
J2: Conn_01x04_Socket; PinSocket_1x4
J3: Conn_01x08_Socket; PinSocket_1x8
J4: Conn_01x05_Socket; PinSocket_1x5
R1: 10, 1%; RESC0603
R2: 1G, 5%, 0603; RESC0603
U1: AD8615

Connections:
/2.5V: C1.1, J2.1, U1.5 (V+)
/-1.5V: C2.1, J2.3, U1.2 (V-)
/AD8615_Output: J4.2, U1.1
/BiasVoltage: J3.5, J3.6, J3.7, J3.8, J4.5
/Current: J3.1, J3.2, J3.3, J3.4, R2.1, U1.4 (-)
/ISO_GND: J1.2, J4.1, J4.4, U1.3 (+)
/PreVoltage: J4.3, R2.2
GND: C1.2, C2.2, J1.1, J2.2, J2.4, R1.2
unnamed: J1.3, R1.1

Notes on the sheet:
Excluded from BOM because already have 3 spares in stock from Phase 0.1

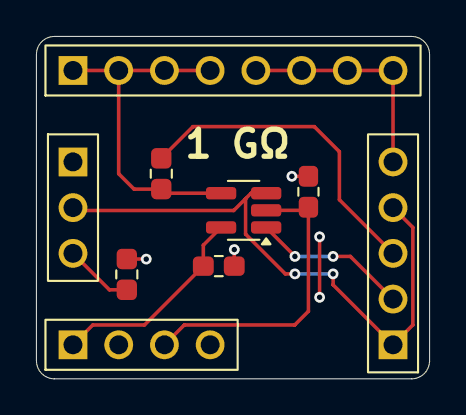
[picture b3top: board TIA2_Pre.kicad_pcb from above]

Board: 2 copper layers, 21.8 x 19.0 mm, 9 parts (0 on the bottom side), 9 nets.

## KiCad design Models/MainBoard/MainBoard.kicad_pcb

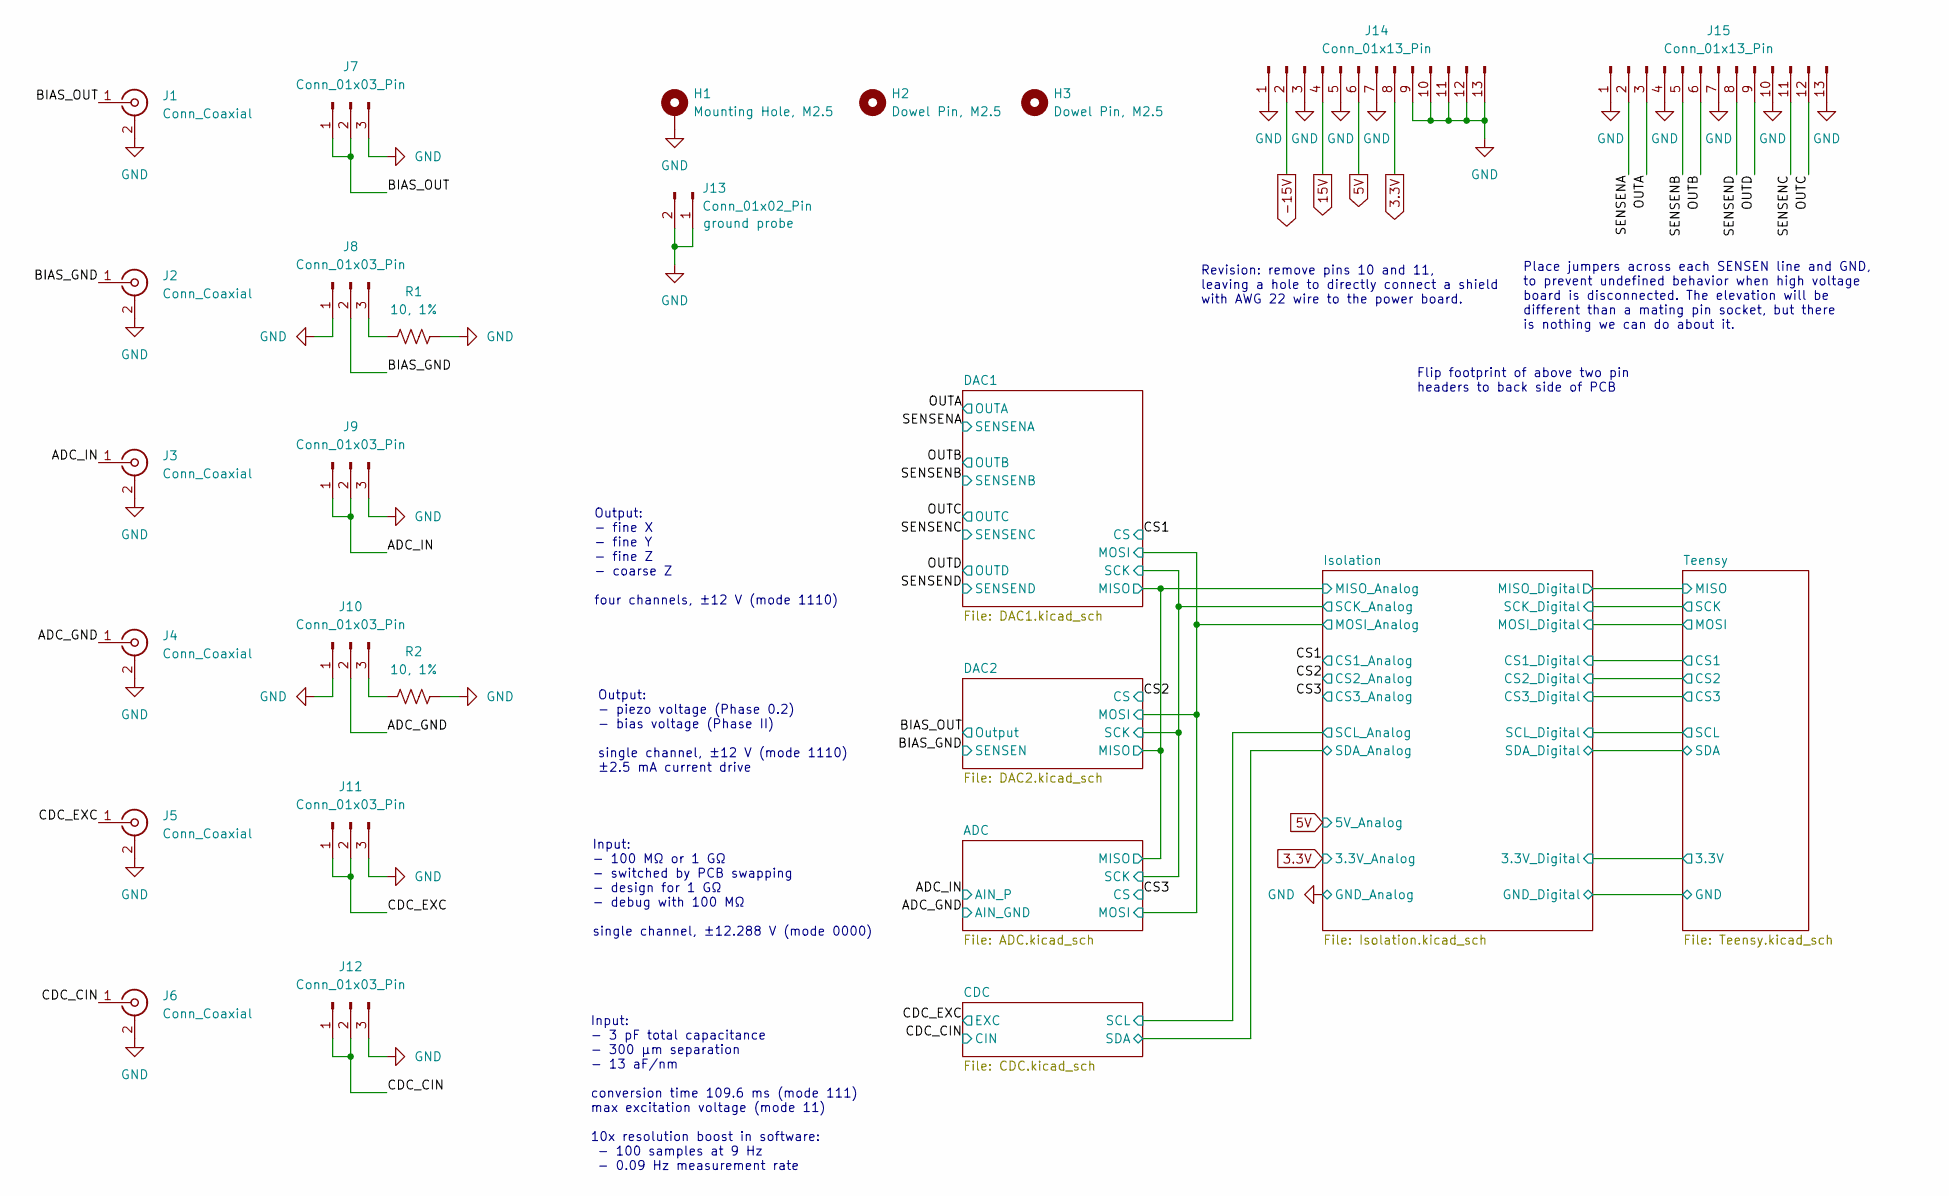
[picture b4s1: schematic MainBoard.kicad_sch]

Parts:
H1: Mounting Hole, M2.5; Keystone_24929
H2, H3: Dowel Pin, M2.5; DowelPin_2.5mm
J1, J2, J3, J4, J5, J6: Conn_Coaxial; Molex_MCX
J7, J8, J9, J10, J11, J12: Conn_01x03_Pin; PinHeader_1x3
J13: Conn_01x02_Pin; PinHeader_1x2
J14, J15: Conn_01x13_Pin; PinHeader_1x13
R1, R2: 10, 1%; RESC0603

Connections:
3.3V: J14.8; also elsewhere on the board
5V: J14.6; also elsewhere on the board
15V: J14.4; also elsewhere on the board
-15V: J14.2; also elsewhere on the board
/ADC_GND: J4.1 (In), J10.2; also elsewhere on the board
/ADC_IN: J3.1 (In), J9.1, J9.2; also elsewhere on the board
/BIAS_GND: J2.1 (In), J8.2; also elsewhere on the board
/BIAS_OUT: J1.1 (In), J7.1, J7.2; also elsewhere on the board
/CDC_CIN: J6.1 (In), J12.1, J12.2; also elsewhere on the board
/CDC_EXC: J5.1 (In), J11.1, J11.2; also elsewhere on the board
/OUTA: J15.3; also elsewhere on the board
/OUTB: J15.6; also elsewhere on the board
/OUTC: J15.12; also elsewhere on the board
/OUTD: J15.9; also elsewhere on the board
/SENSENA: J15.2; also elsewhere on the board
/SENSENB: J15.5; also elsewhere on the board
/SENSENC: J15.11; also elsewhere on the board
/SENSEND: J15.8; also elsewhere on the board
GND: H1.1, J1.2 (Ext), J2.2 (Ext), J3.2 (Ext), J4.2 (Ext), J5.2 (Ext), J6.2 (Ext), J7.3, J8.1, J9.3, J10.1, J11.3, J12.3, J13.1, J13.2, J14.1, J14.3, J14.5, J14.7, J14.9, J14.10, J14.11, J14.12, J14.13, J15.1, J15.4, J15.7, J15.10, J15.13, R1.2, R2.2; also elsewhere on the board
unnamed: J8.3, R1.1
unnamed: J10.3, R2.1

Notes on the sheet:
Output: - piezo voltage (Phase 0.2) - bias voltage (Phase II) single channel, ±12 V (mode 1110) ±2.5 mA current drive
Revision: remove pins 10 and 11, leaving a hole to directly connect a shield with AWG 22 wire to the power board.
Output: - fine X - fine Y - fine Z - coarse Z four channels, ±12 V (mode 1110)
Flip footprint of above two pin headers to back side of PCB
Input: - 100 MΩ or 1 GΩ - switched by PCB swapping - design for 1 GΩ - debug with 100 MΩ single channel, ±12.288 V (mode 0000)
Place jumpers across each SENSEN line and GND, to prevent undefined behavior when high voltage board is disconnected. The elevation will be different than a mating pin socket, but there is nothing we can do about it.
Input: - 3 pF total capacitance - 300 μm separation - 13 aF/nm conversion time 109.6 ms (mode 111) max excitation voltage (mode 11) 10x resolution boost in software: - 100 samples at 9 Hz - 0.09 Hz measurement rate
